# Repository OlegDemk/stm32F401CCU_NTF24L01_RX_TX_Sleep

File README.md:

The project base on STM32F401CCU microcontroller and NRF24L01 radio module. Project was create on STM32 Cube IDE. 
The RX project: TR all time listen TX modules(up to 6), mark from witch PIPE was(from what TX module data transmeeted), and transmeet reseived data into UART. 

The TX project: Transmeet this data: (32 bytes/one packet)
1. Temperature, Humidity from BME280.
2. Battery voltage. 
3. Retransmitted data packets counter and lost data packets counter. (need for detect lost packets).
After data transmeeting, TX devise go into Stenby mode.
The power consumption(STM32+NRF24l01+BME280) into this mode around 37uA, in condition when device woke up every 5 seconds, and transmeet data every 60 seconds.

Power Consumption

Data:

Settings located on the main.h file

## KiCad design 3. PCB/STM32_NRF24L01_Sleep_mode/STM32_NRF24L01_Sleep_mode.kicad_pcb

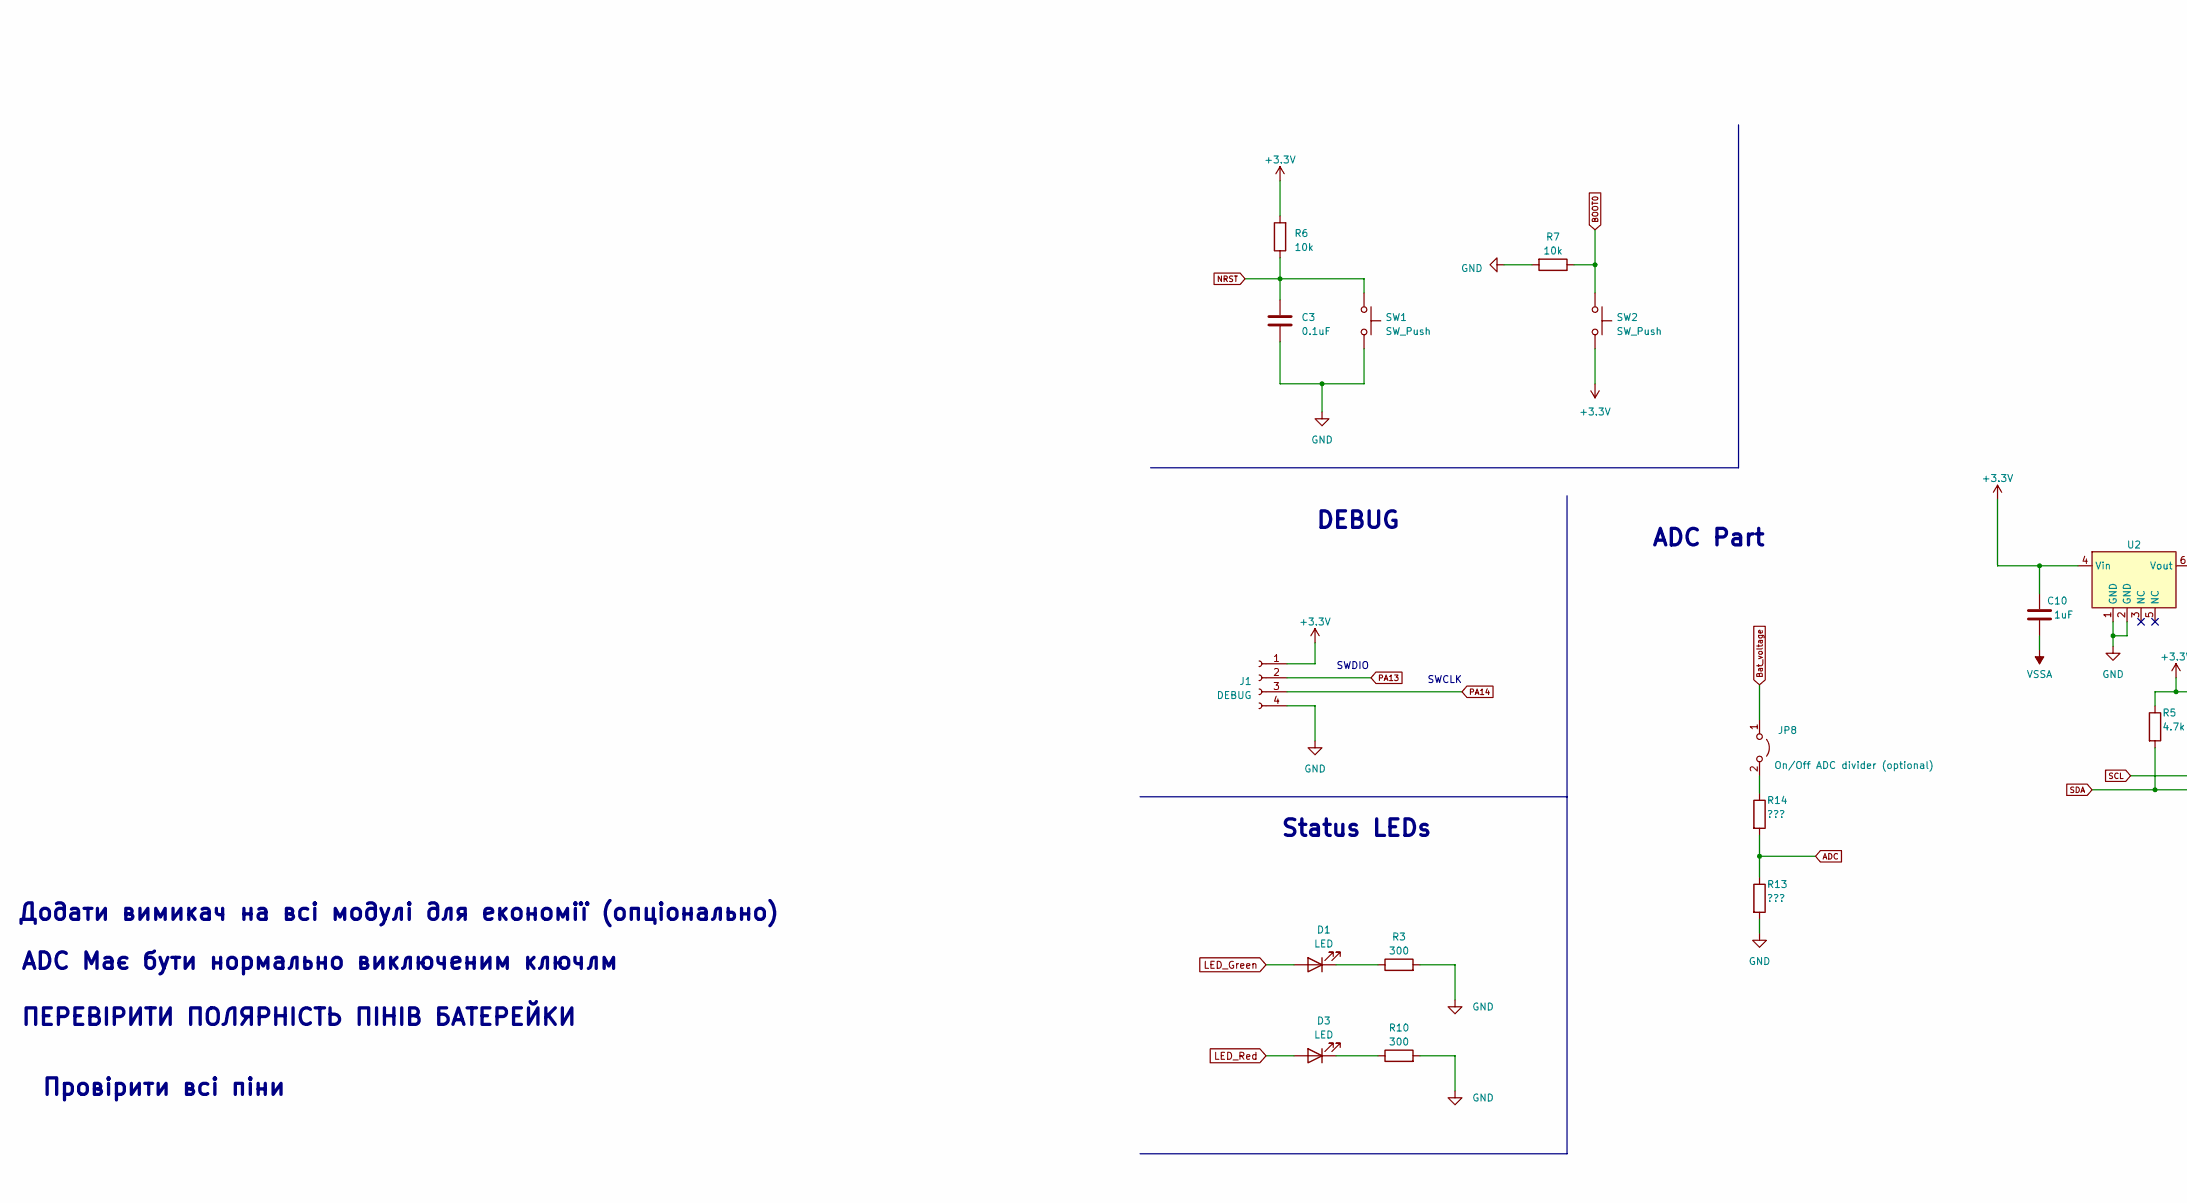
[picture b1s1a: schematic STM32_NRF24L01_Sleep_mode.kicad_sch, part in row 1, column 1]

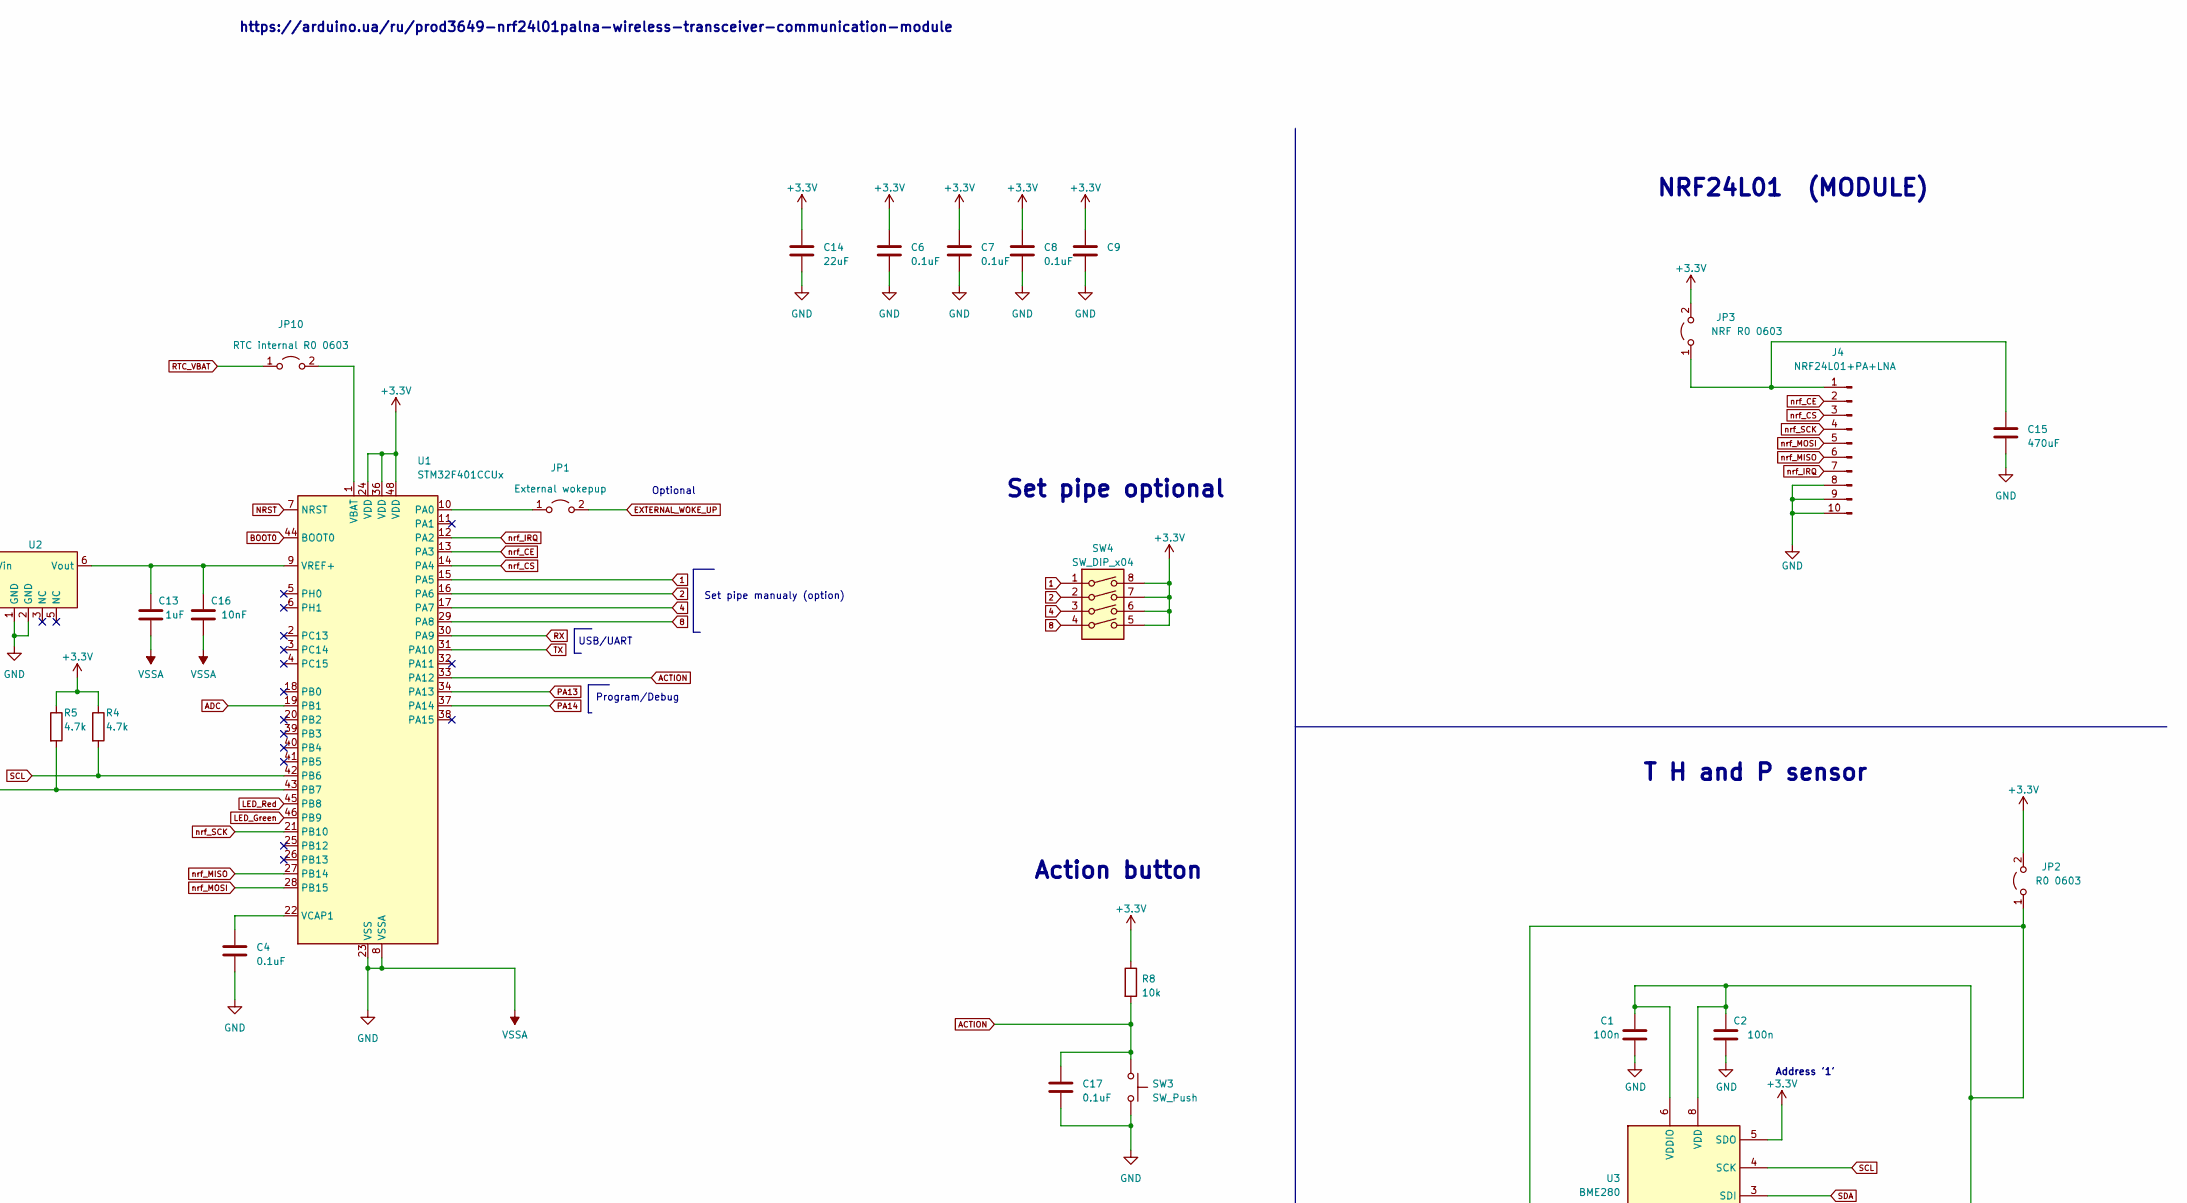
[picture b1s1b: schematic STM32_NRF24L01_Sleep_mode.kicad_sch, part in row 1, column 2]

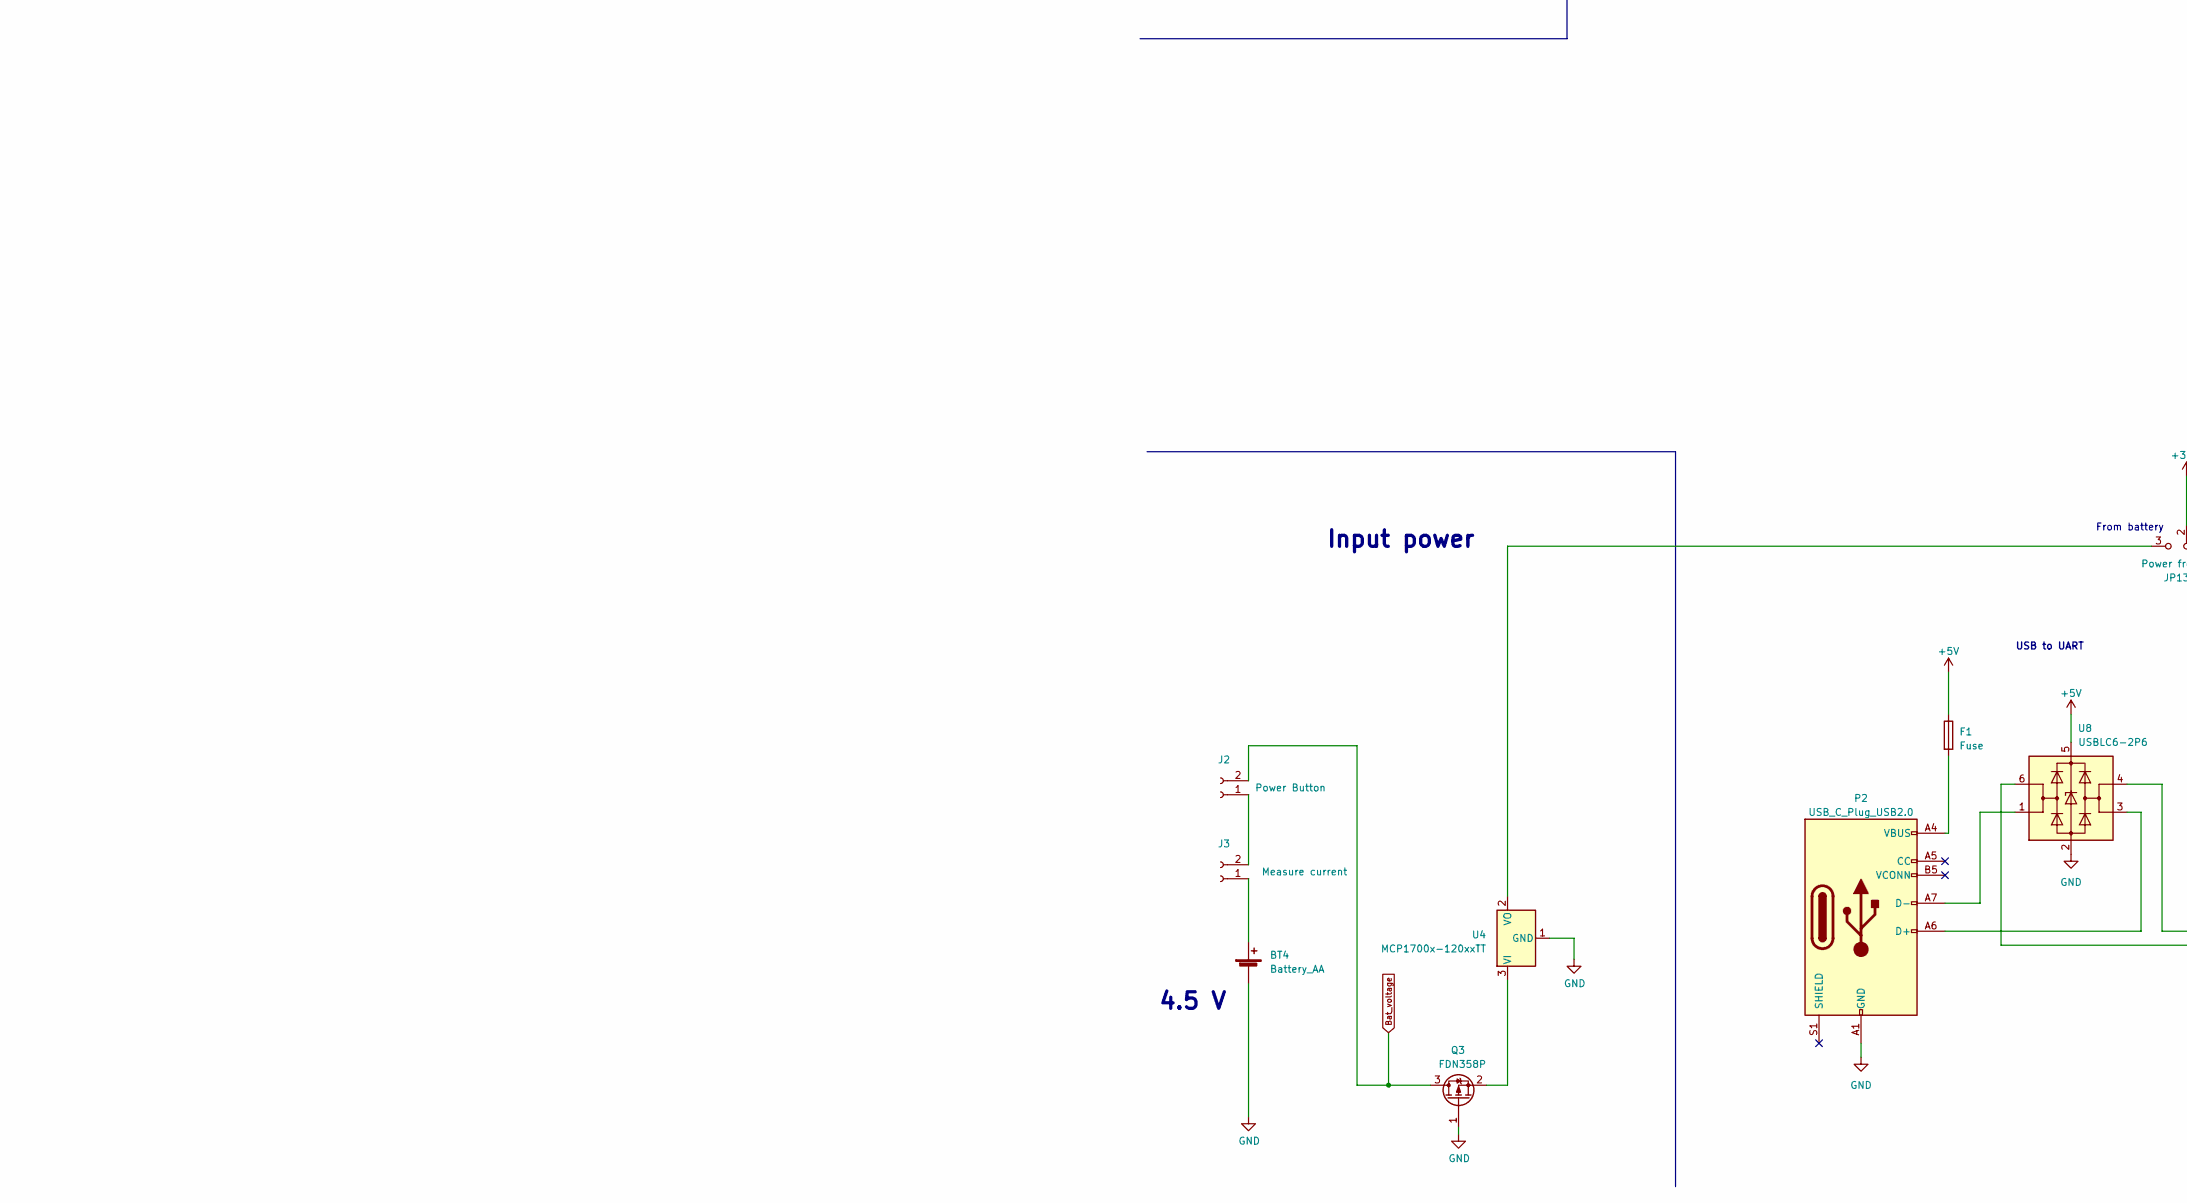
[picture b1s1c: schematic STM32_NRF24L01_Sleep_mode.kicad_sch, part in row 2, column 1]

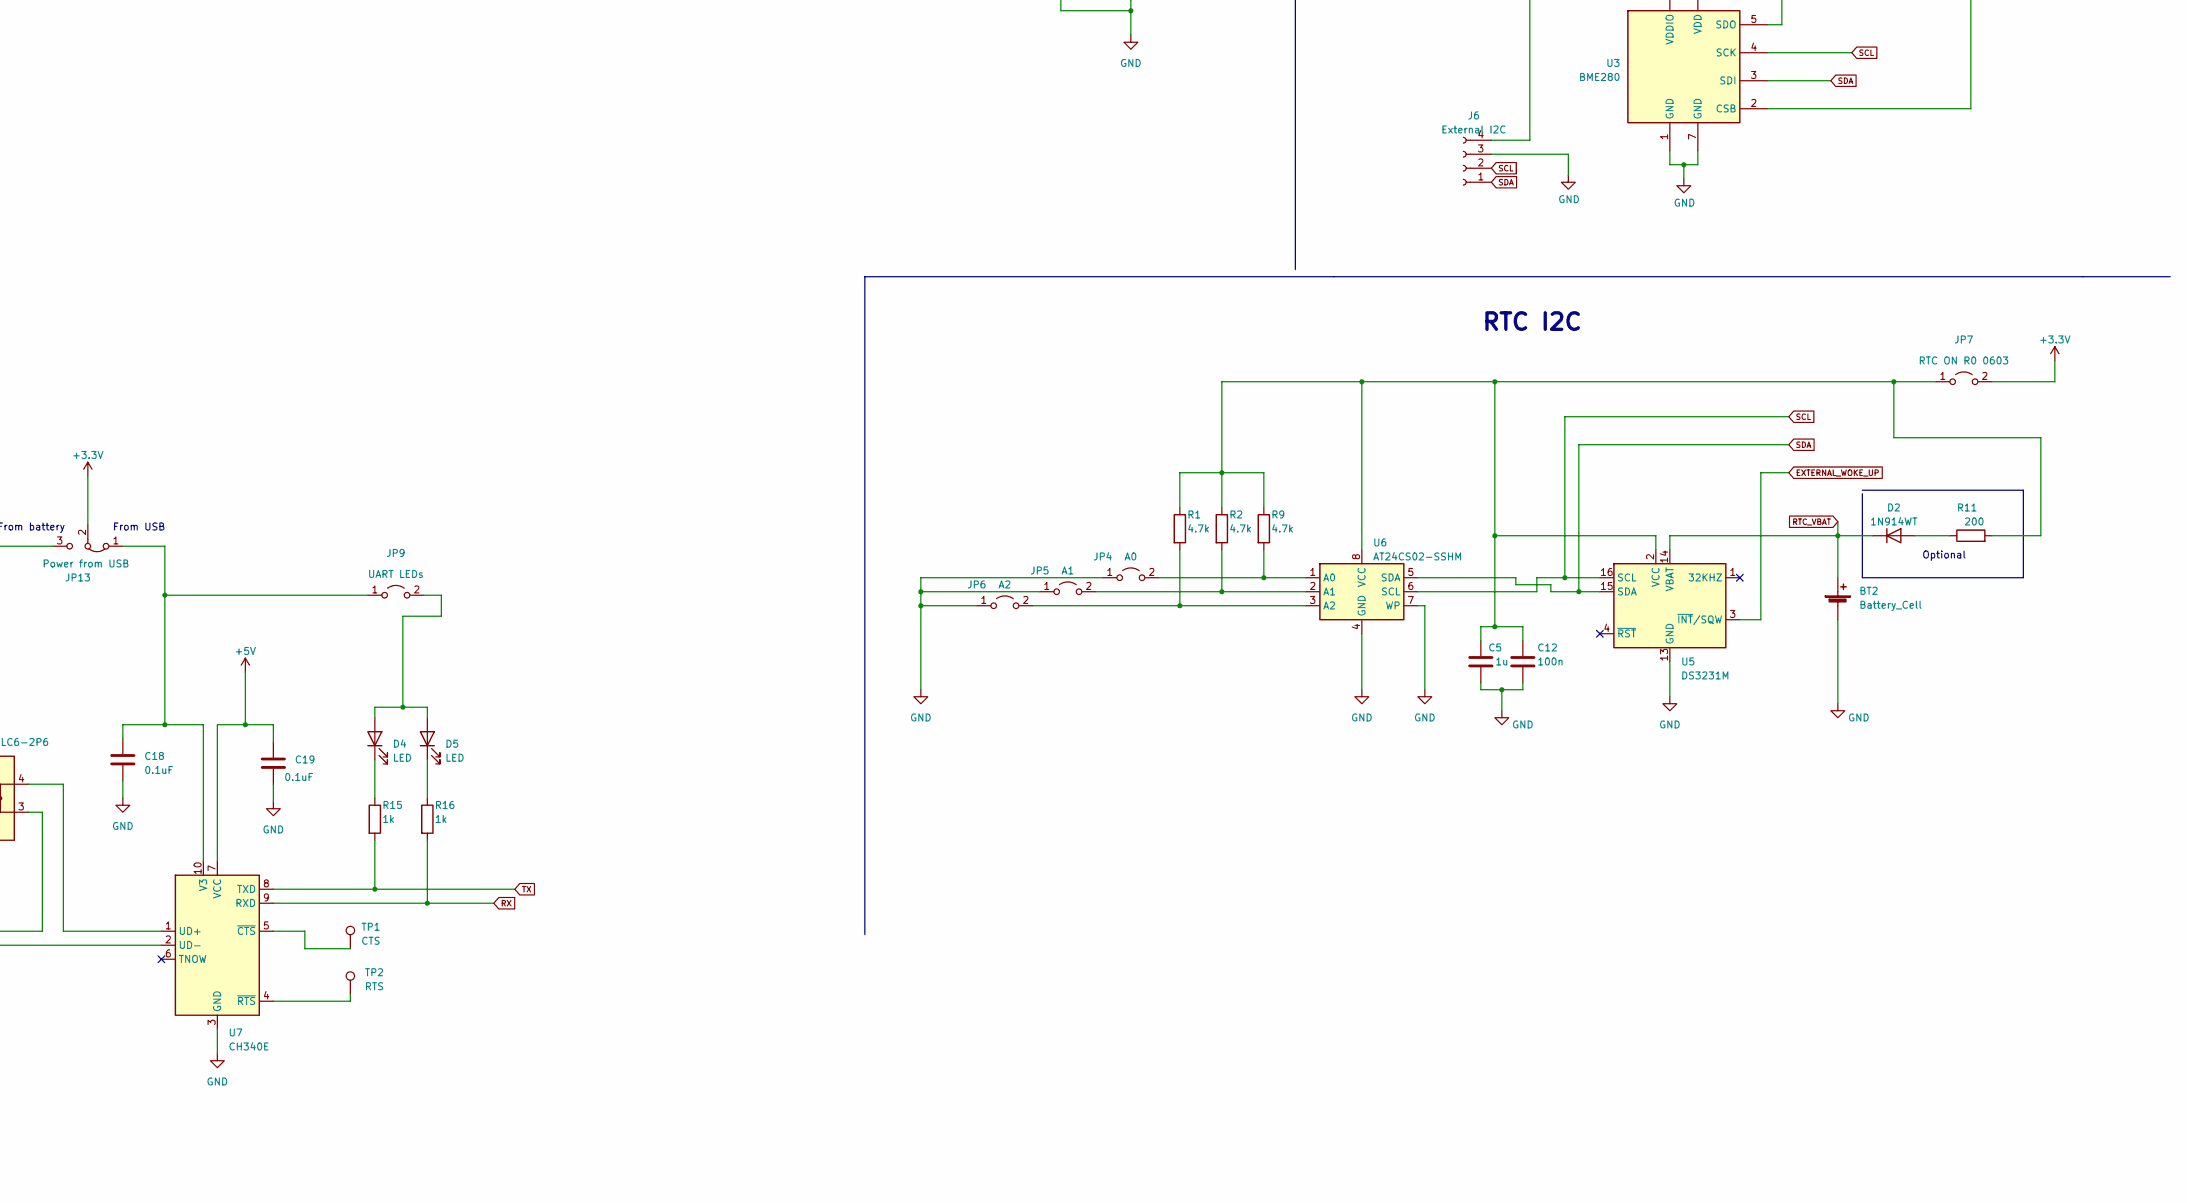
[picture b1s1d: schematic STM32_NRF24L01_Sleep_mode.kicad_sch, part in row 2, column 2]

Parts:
BT2: Battery_Cell; BatteryHolder_MPD_BC2003_1x2032
BT4: Battery_AA; 3X_AA_holder
C1, C2, C12: 100n; C_0603_1608Metric_Pad1.08x0.95mm_HandSolder
C3, C4, C6, C7, C8, C9, C17, C18, C19: 0.1uF; C_0603_1608Metric_Pad1.08x0.95mm_HandSolder
C5: 1u; C_0603_1608Metric_Pad1.08x0.95mm_HandSolder
C10, C13: 1uF; C_0603_1608Metric_Pad1.08x0.95mm_HandSolder
C14: 22uF; R_0805_2012Metric_Pad1.20x1.40mm_HandSolder
C15: 470uF; CP_EIA-7343-31_Kemet-D
C16: 10nF; C_0603_1608Metric_Pad1.08x0.95mm_HandSolder
D1, D3, D4, D5: LED; LED_0402_1005Metric_Pad0.77x0.64mm_HandSolder
D2: 1N914WT; D_MiniMELF
F1: Fuse; Fuse_0603_1608Metric_Pad1.05x0.95mm_HandSolder
J1: DEBUG; PinHeader_1x04_P2.54mm_Vertical_SMD_Pin1Right
J2: Power Button; PinSocket_1x02_P2.54mm_Vertical_SMD_Pin1Left
J3: Measure current; PinSocket_1x02_P2.54mm_Vertical_SMD_Pin1Left
J4: NRF24L01+PA+LNA; NRF24L01
J6: External I2C; PinHeader_1x04_P2.54mm_Vertical_SMD_Pin1Left
JP1: External wokepup; R_0603_1608Metric_Pad0.98x0.95mm_HandSolder
JP2: R0 0603; R_0603_1608Metric_Pad0.98x0.95mm_HandSolder
JP3: NRF R0 0603; R_0603_1608Metric_Pad0.98x0.95mm_HandSolder
JP4: A0; SolderJumper-2_P1.3mm_Open_TrianglePad1.0x1.5mm
JP5: A1; SolderJumper-2_P1.3mm_Open_TrianglePad1.0x1.5mm
JP6: A2; SolderJumper-2_P1.3mm_Open_TrianglePad1.0x1.5mm
JP7: RTC ON R0 0603; R_0603_1608Metric_Pad0.98x0.95mm_HandSolder
JP8: On/Off ADC divider (optional); R_0603_1608Metric_Pad0.98x0.95mm_HandSolder
JP9: UART LEDs; R_0603_1608Metric_Pad0.98x0.95mm_HandSolder
JP10: RTC internal R0 0603; R_0603_1608Metric_Pad0.98x0.95mm_HandSolder
JP13: Power from USB; PinHeader_1x03_P2.54mm_Vertical_SMD_Pin1Right
P2: USB_C_Plug_USB2.0; USB_C_Receptacle_G-Switch_GT-USB-7010ASV
Q3: FDN358P; SOT-23
R1, R2, R4, R5, R9: 4.7k; R_0603_1608Metric_Pad0.98x0.95mm_HandSolder
R3, R10: 300; R_0603_1608Metric_Pad0.98x0.95mm_HandSolder
R6, R7, R8: 10k; R_0603_1608Metric_Pad0.98x0.95mm_HandSolder
R11: 200; R_0603_1608Metric_Pad0.98x0.95mm_HandSolder
R13, R14: ???; R_0603_1608Metric_Pad0.98x0.95mm_HandSolder
R15, R16: 1k; R_0603_1608Metric_Pad0.98x0.95mm_HandSolder
SW1, SW2, SW3: SW_Push; SW_Push_SPST_NO_Alps_SKRK
SW4: SW_DIP_x04; DIP_nuttons_4x
TP1: CTS; TestPoint_Pad_2.0x2.0mm
TP2: RTS; TestPoint_Pad_2.0x2.0mm
U1: STM32F401CCUx; QFN-48-1EP_7x7mm_P0.5mm_EP5.6x5.6mm
U2: SOT-23-6_Handsoldering
U3: BME280; Bosch_LGA-8_2.5x2.5mm_P0.65mm_ClockwisePinNumbering
U4: MCP1700x-120xxTT; SOT-23
U5: DS3231M; SOIC-16W_7.5x10.3mm_P1.27mm
U6: AT24CS02-SSHM; SOIC-8_3.9x4.9mm_P1.27mm
U7: CH340E; MSOP-10_3x3mm_P0.5mm
U8: USBLC6-2P6; SOT-666

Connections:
1: SW4.1, U1.15 (PA5)
2: SW4.2, U1.16 (PA6)
4: SW4.3, U1.17 (PA7)
8: SW4.4, U1.29 (PA8)
+3.3V: C6.1, C7.1, C8.1, C9.1, C10.1, C14.1, J1.1, JP2.2 (B), JP3.2 (B), JP7.2 (B), JP13.2 (C), R4.1, R5.1, R6.2, R8.1, SW2.2, SW4.5, SW4.6, SW4.7, SW4.8, U1.24 (VDD), U1.36 (VDD), U1.48 (VDD), U2.4 (Vin), U3.5 (SDO)
+5V: C19.1, F1.1, U7.7 (VCC), U8.5 (VBUS)
ACTION: C17.1, R8.2, SW3.1, U1.33 (PA12)
ADC: R13.1, R14.2, U1.19 (PB1)
BOOT0: R7.1, SW2.1, U1.44 (BOOT0)
Bat_voltage: J2.2, JP8.1 (A), Q3.3 (D)
EXTERNAL_WOKE_UP: JP1.2 (B), U5.3 (~INT/SQW)
GND: BT2.2 (-), BT4.2 (-), C1.2, C2.2, C3.2, C4.2, C5.2, C6.2, C7.2, C8.2, C9.2, C10.2, C12.2, C13.2, C14.2, C15.2, C16.2, C17.2, C18.2, C19.2, J1.4, J4.8, J4.9, J4.10, J6.3, JP4.1 (A), JP5.1 (A), JP6.1 (A), P2.A1 (GND), P2.A12 (GND), P2.B1 (GND), P2.B12 (GND), Q3.1 (G), R3.2, R7.2, R10.2, R13.2, SW1.2, SW3.2, U1.8 (VSSA), U1.23 (VSS), U1.35 (VSS), U1.47 (VSS), U1.49 (VSS), U2.1 (GND), U2.2 (GND), U3.1 (GND), U3.7 (GND), U4.1 (GND), U5.5 (GND), U5.6 (GND), U5.7 (GND), U5.8 (GND), U5.9 (GND), U5.10 (GND), U5.11 (GND), U5.12 (GND), U5.13 (GND), U6.4 (GND), U6.7 (WP), U7.3 (GND), U8.2 (GND)
LED_Green: D1.2 (A), U1.46 (PB9)
LED_Red: D3.2 (A), U1.45 (PB8)
NRST: C3.1, R6.1, SW1.1, U1.7 (NRST)
unnamed: BT4.1 (+), J3.1
unnamed: D1.1 (K), R3.1
unnamed: D2.2 (A), R11.1
unnamed: D3.1 (K), R10.1
unnamed: D4.2 (A), D5.2 (A), JP9.2 (B)
unnamed: D4.1 (K), R15.1
unnamed: D5.1 (K), R16.1
unnamed: F1.2, P2.A4 (VBUS), P2.A9 (VBUS), P2.B4 (VBUS), P2.B9 (VBUS)
unnamed: J2.1, J3.2
unnamed: C15.1, J4.1, JP3.1 (A)
unnamed: C1.1, C2.1, J6.4, JP2.1 (A), U3.2 (CSB), U3.6 (VDDIO), U3.8 (VDD)
unnamed: JP1.1 (A), U1.10 (PA0)
unnamed: JP4.2 (B), R9.2, U6.1 (A0)
unnamed: JP5.2 (B), R2.2, U6.2 (A1)
unnamed: JP6.2 (B), R1.2, U6.3 (A2)
unnamed: C5.1, C12.1, JP7.1 (A), R1.1, R2.1, R9.1, R11.2, U5.2 (VCC), U6.8 (VCC)
unnamed: JP8.2 (B), R14.1
unnamed: JP10.2 (B), U1.1 (VBAT)
unnamed: C18.1, JP9.1 (A), JP13.1 (A), U7.10 (V3)
unnamed: JP13.3 (B), U4.2 (VO)
unnamed: P2.A6 (D+), U8.3 (I/O2)
unnamed: P2.A7 (D-), U8.1 (I/O1)
unnamed: Q3.2 (S), U4.3 (VI)
unnamed: C4.1, U1.22 (VCAP1)
unnamed: C13.1, C16.1, U1.9 (VREF+), U2.6 (Vout)
unnamed: U7.1 (UD+), U8.4 (I/O2)
unnamed: U7.2 (UD-), U8.6 (I/O1)
unnamed: TP1.1, U7.5 (~CTS)
unnamed: TP2.1, U7.4 (~RTS)
PA13: J1.2, U1.34 (PA13)
PA14: J1.3, U1.37 (PA14)
RTC_VBAT: BT2.1 (+), D2.1 (K), JP10.1 (A), U5.14 (VBAT)
RX: R16.2, U1.30 (PA9), U7.9 (RXD)
SCL: J6.2, R4.2, U1.42 (PB6), U3.4 (SCK), U5.16 (SCL), U6.6 (SCL)
SDA: J6.1, R5.2, U1.43 (PB7), U3.3 (SDI), U5.15 (SDA), U6.5 (SDA)
TX: R15.2, U1.31 (PA10), U7.8 (TXD)
nrf_CE: J4.2, U1.13 (PA3)
nrf_CS: J4.3, U1.14 (PA4)
nrf_IRQ: J4.7, U1.12 (PA2)
nrf_MISO: J4.6, U1.27 (PB14)
nrf_MOSI: J4.5, U1.28 (PB15)
nrf_SCK: J4.4, U1.21 (PB10)

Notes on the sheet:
ПЕРЕВІРИТИ ПОЛЯРНІСТЬ ПІНІВ БАТЕРЕЙКИ
Set pipe manualy (option)
SWDIO
NRF24L01 (MODULE)
4.5 V
T H and P sensor
ADC Part
Status LEDs
Address '1'
ADC Має бути нормально виключеним ключлм
Додати вимикач на всі модулі для економії (опціонально)
USB to UART
https://arduino.ua/ru/prod3649-nrf24l01palna-wireless-transceiver-communication-module
From USB
From battery
Провірити всі піни
USB/UART
Input power
RTC I2C
DEBUG
Program/Debug
Set pipe optional
SWCLK
Optional
Action button

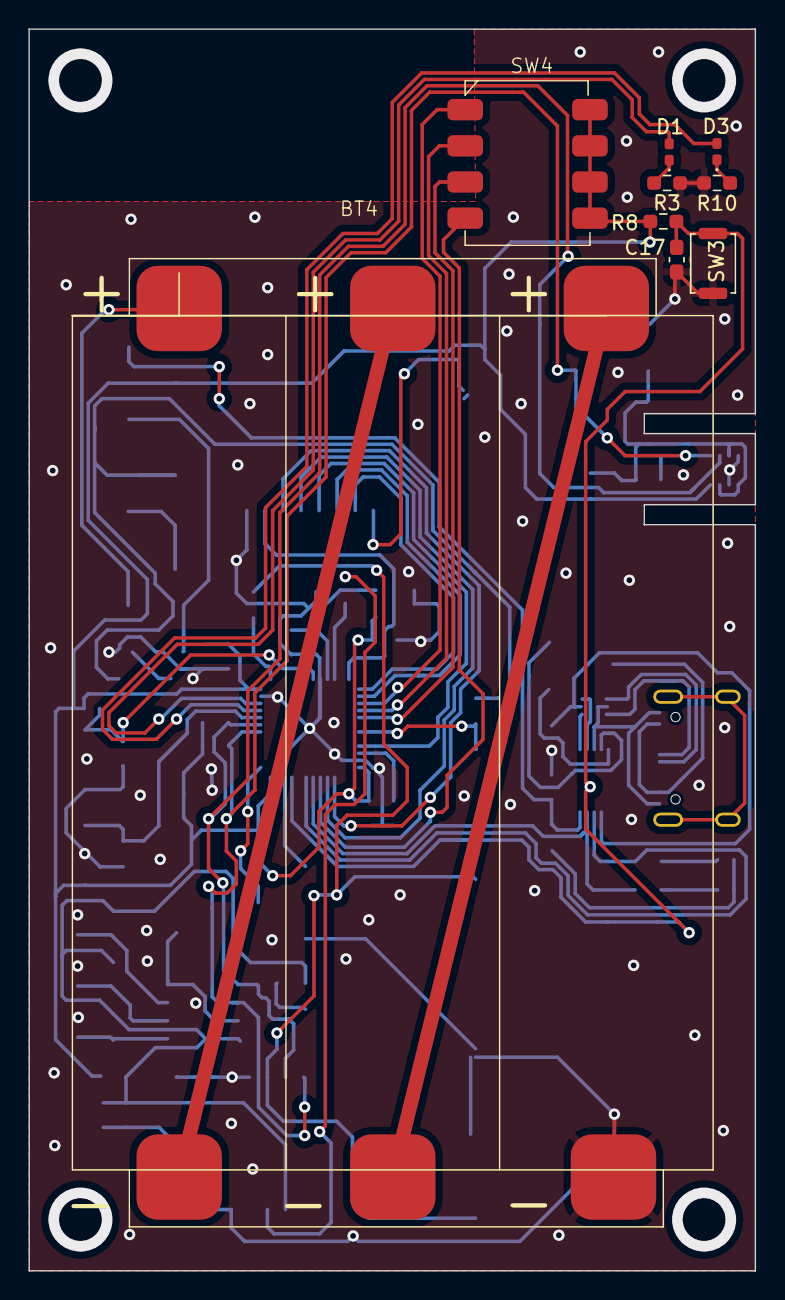
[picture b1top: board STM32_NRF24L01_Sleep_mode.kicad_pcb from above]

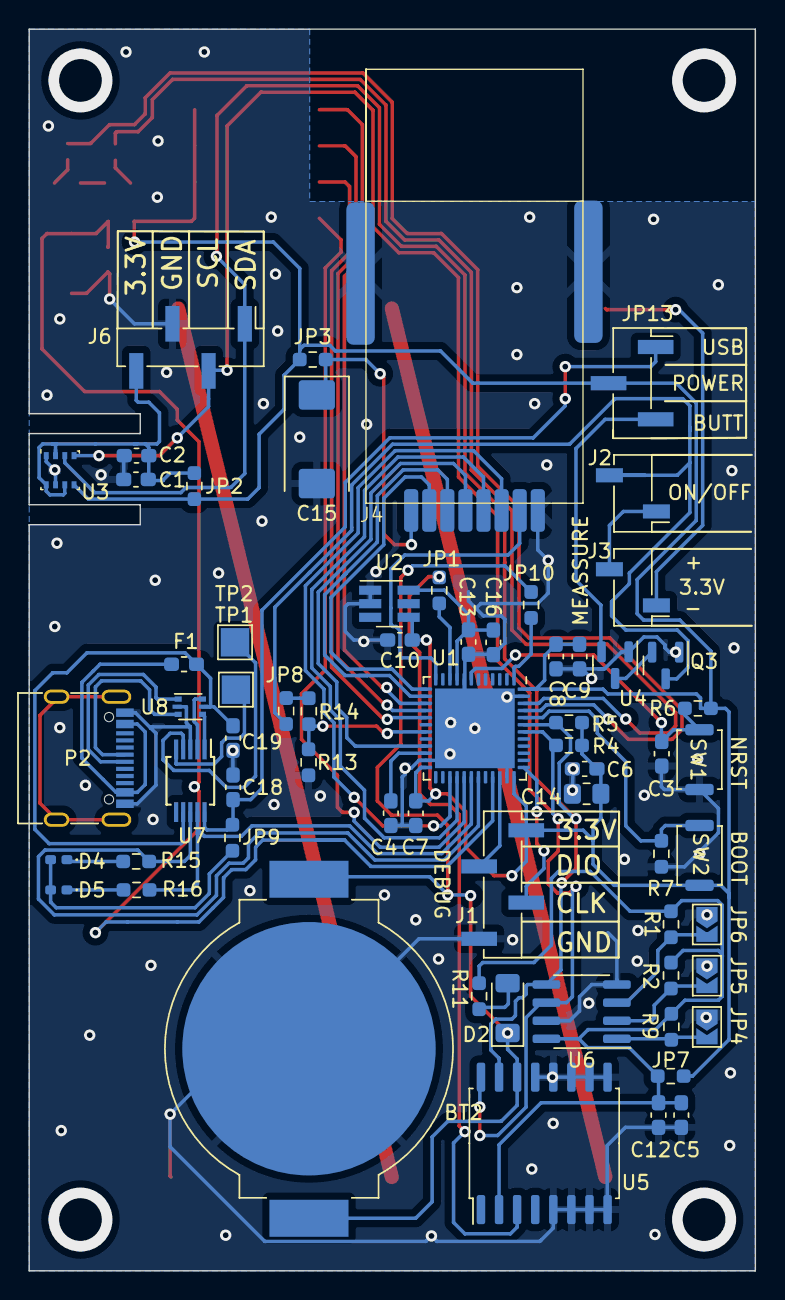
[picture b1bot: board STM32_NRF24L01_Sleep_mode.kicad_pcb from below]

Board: 2 copper layers, 51.0 x 87.2 mm, 73 parts (64 on the bottom side), 57 nets.

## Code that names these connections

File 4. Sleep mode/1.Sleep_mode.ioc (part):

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Mcu.Name=STM32F401C(B-C)Ux
Mcu.Package=UFQFPN48
Mcu.UserName=STM32F401CCUx
PA0-WKUP.Mode=SYS_WakeUp0
PA0-WKUP.Signal=SYS_WKUP
PA10.Mode=Asynchronous
PA10.Signal=USART1_RX
PA12.GPIOParameters=GPIO_Label
PA12.GPIO_Label=ACTION
PA12.Signal=GPIO_Input
PA13.Mode=Serial_Wire
PA13.Signal=SYS_JTMS-SWDIO
PA14.Mode=Serial_Wire
PA14.Signal=SYS_JTCK-SWCLK
PA2.GPIOParameters=GPIO_Label,GPIO_ModeDefaultEXTI
PA2.GPIO_Label=nrf_IRQ
PA2.GPIO_ModeDefaultEXTI=GPIO_MODE_IT_FALLING
PA2.Signal=GPXTI2
PA3.GPIOParameters=GPIO_Label
PA3.GPIO_Label=nrf_CE
PA3.Signal=GPIO_Output
PA4.GPIOParameters=GPIO_Label
PA4.GPIO_Label=nrf_CS
PA4.Signal=GPIO_Output
PA9.Mode=Asynchronous
PA9.Signal=USART1_TX
PB1.Signal=ADCx_IN9
PB10.Mode=Full_Duplex_Master
PB10.Signal=SPI2_SCK
PB14.Mode=Full_Duplex_Master
PB14.Signal=SPI2_MISO
PB15.Mode=Full_Duplex_Master
PB15.Signal=SPI2_MOSI
PB6.Mode=I2C
PB6.Signal=I2C1_SCL
PB7.Mode=I2C
PB7.Signal=I2C1_SDA
PB8.GPIOParameters=GPIO_Label
PB8.GPIO_Label=LED_Red
PB8.Signal=GPIO_Output
PB9.GPIOParameters=GPIO_Label
PB9.GPIO_Label=LED_Green
PB9.Signal=GPIO_Output
RCC.HSE_VALUE=25000000
RCC.SYSCLKFreq_VALUE=64000000
RCC.SYSCLKSource=RCC_SYSCLKSOURCE_PLLCLK
board=custom

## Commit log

2024-06-11 V1.0
2024-06-11 RX update
2024-06-11 Two TX devices was added
2024-06-12 Diagram has been added
2024-06-12 Refactoring code
2024-06-13 TX on sleep mode, 0,240 mA with external RTC, Transmit data every 20 sec
2024-06-13 Microcontroller friquenses was decrease from 64 MHz to 8 MHz. Power consumption is 0.210 mA
2024-06-17 Update TX dev, use internal RTC, power cunsumption 50 uA
2024-06-17 ref TX project
2024-06-26 Tx and Rx only, power consumption 40uA
2024-06-26 power consumprion measure was added
2024-06-26 pictures was added
